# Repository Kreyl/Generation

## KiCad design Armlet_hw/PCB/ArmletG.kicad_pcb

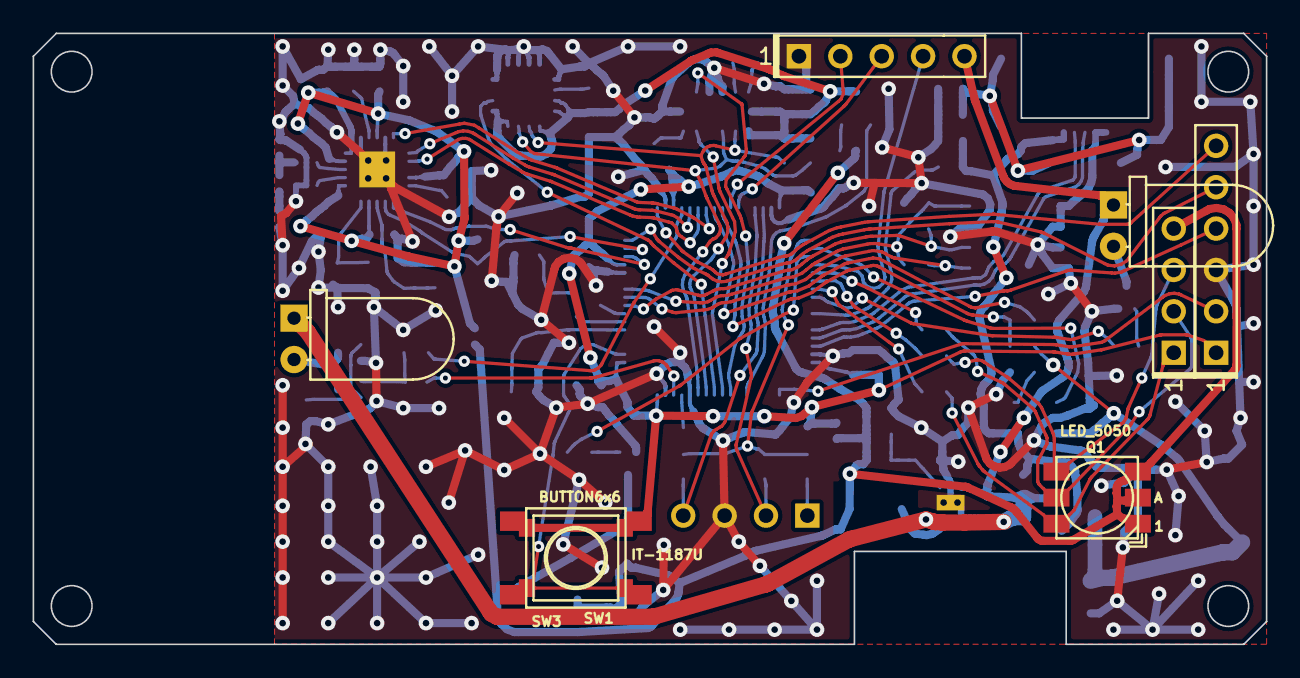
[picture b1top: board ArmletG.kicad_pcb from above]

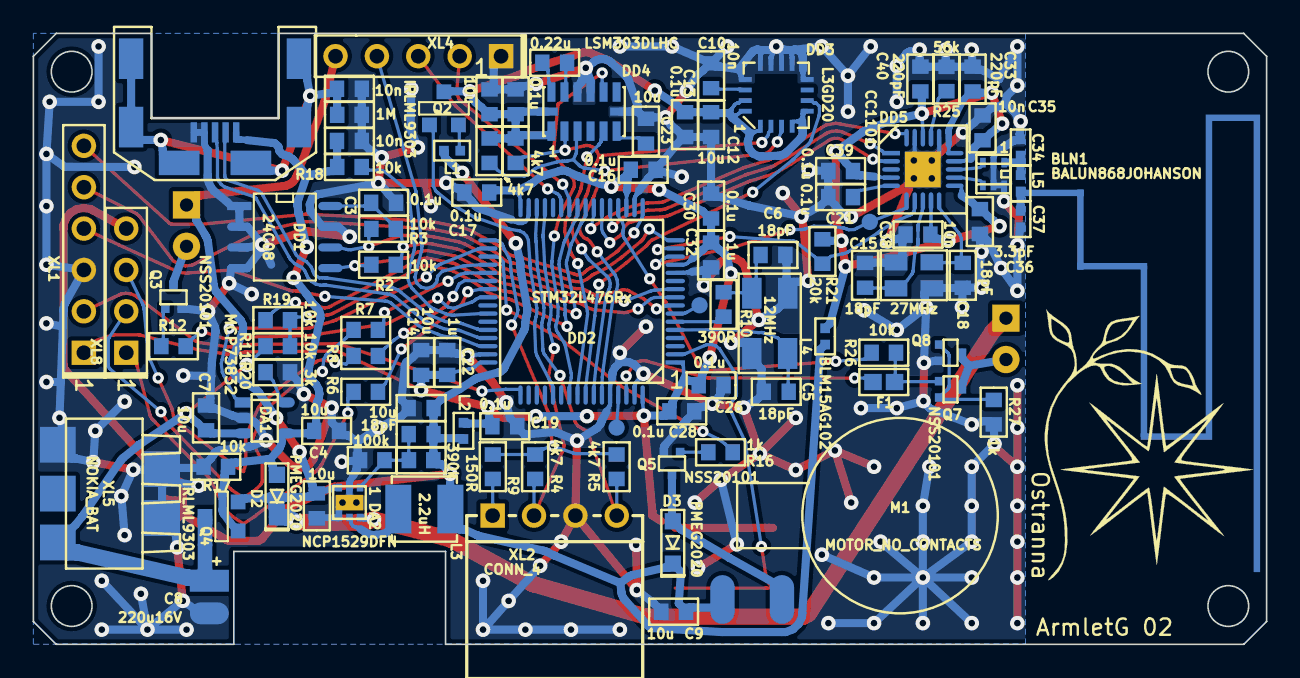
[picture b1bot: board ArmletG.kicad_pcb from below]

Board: 2 copper layers, 75.7 x 37.5 mm, 107 parts (102 on the bottom side), 79 nets.

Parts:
ANT1: ANT_PCB_MONO; ANT_868_ARMLETG
BLN1: BALUN868JOHANSON; BALUN_JOHANSON868
C1, C2, C10, C35, C38: 10n; CAP_0603
C3, C13, C16, C17, C19, C21, C26, C28, C30, C31, C39: 0.1u; CAP_0603
C4, C7, C9, C11, C12, C14, C23, C24, C29: 10u; CAP_0603
C5, C6, C15, C18, C20: 18pF; CAP_0603
C8: 220u16V; CAP_05xxR_horiz_HOLE
C22, C32: 1u; CAP_0603
C25: 0.22u; CAP_0603
C33, C40: 220pF; CAP_0603
C34, C37: *; CAP_0402
C36: 3.3pF; CAP_0603
D1: WhiteLED; LED_Through-Hole-5mm-HOR
D2, D3: PMEG2020; SOD323
D4: LED; LED_Through-Hole-5mm-HOR
DA1: MCP73832; SOT23-5
DA2: NCP1529DFN; DFN6
DD1: 24C08; SO8_150MIL
DD2: STM32L476Rx; LQFP64
DD3: L3GD20; 16_4X4_P065
DD4: LSM303DLHC; 14_5X3_P08
DD5: CC1101; QFN20
F1: Fuse0R; RES_0603_FUSE
L1, L2, L4: BLM15AG102; IND_0402
L3: 2.2uH; IND_1515
L5: *; IND_0402
Logo1: Logo; Ostranna_16d9_13d5
M1: MOTOR_NO_CONTACTS; Motor_no_Contacts
Q1: LED_5050
Q2, Q4: IRLML9303; SOT23-3
Q3, Q5, Q7, Q8: NSS20101; SC89-3
R1: 1M; RES_0603
R2, R3, R17, R18, R19, R20, R26: 10k; RES_0603
R4, R5, R13, R14: 4k7; RES_0603
R6, R7, R8, R12: *; RES_0603
R9: 150R; RES_0603
R10: 390R; RES_0603
R11: 3k; RES_0603
R16, R27: 1k; RES_0603
R21: 20k; RES_0603
R22: 390k; RES_0603
R23: 100k; RES_0603
R25: 56k; RES_0603
SW1: IT-1187U; BTN_4x4_SMD
SW3: BUTTON6x6; BTN_6x6
TP1, TP2, TP3: TESTPOINT; TESTPOINT_1MM
XL1: CONN_6; PLS-6
XL2: CONN_4; PBS-4R
XL3: USB_Micro_B; USBmicro_MOLEX_WM17142
XL4: CONN_5; PLS-5
XL5: NOKIA_BAT; CONN_NOKIA_ACC
XL6, XL7: CONN_1; Oval3x1.5
XL8: CONN_4; PLS-4
XTAL1: 12MHz; 0503x4-4
XTAL2: 27MHz; 03225C4

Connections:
+3.3V: C9.2, C20.2, C24.2, D3.C, L1.2, L2.2, L3.1, L4.2, Q1.1, Q1.2, Q1.3, R22.1, XL6.1, XL8.4
+5V: C2.2, C4.2, D2.A, DA1.4, Q4.1, R17.1, R18.2, XL3.1
+BATT: C7.2, C8.1, DA1.3, Q4.3, R20.2, XL5.1
/ACC_DRDY: DD2.55, DD4.9
/ACC_INT1: DD2.56, DD4.5
/ANT1: BLN1.1, C34.1, L5.2
/ANT2: ANT1.1, C37.1, L5.1
/BLUE_LED: DD2.39, R6.2
/CC_CS: DD2.15, DD5.7, R21.1
/CC_GDO0: DD2.14, DD5.6, TP3.1
/CC_MISO: DD2.22, DD5.2
/CC_MOSI: DD2.23, DD5.20
/CC_SCK: DD2.21, DD5.1
/Charge: DA1.1, DD2.34
/D+: DD2.45, XL3.3
/D-: DD2.44, XL3.2
/GREEN_LED: DD2.38, R8.2
/GYRO_DRDY: DD2.57, DD3.6
/IR_OUT_DAC: DD2.20, R26.2
/IR_OUT_TIM: DD2.62, F1.2
/IR_TX_OUT: D4.C, Q7.3, Q8.3
/LEDW_CTRL: DD2.40, R12.2
/LEDW_OUT: D1.C, Q3.3
/Lout3V3: DA2.5, L3.2
/PWR_ACC: C12.2, C13.2, C29.2, C31.2, DD3.1, DD3.4, DD3.5, DD3.15, DD3.16, DD4.1, DD4.14, Q2.3, R13.1, R14.1
/PWR_ACC_CTRL: DD2.53, Q2.1
/PWR_EE: C3.2, DD1.8, DD2.10, R2.1, R3.2
/PWR_PILL: DD2.33, R4.1, R5.1, R9.1
/PWR_PILL_PROT: R9.2, XL2.1
/RED_LED: DD2.37, R7.2
/RF1: BLN1.4, DD5.12
/RF2: BLN1.3, DD5.13
/SCL_ACC: DD2.58, DD3.2, DD4.2, R13.2
/SCL_EE: DD1.6, DD2.8, R3.1
/SCL_PILL: DD2.29, R4.2, XL2.2
/SDA_ACC: DD2.59, DD3.3, DD4.3, R14.2
/SDA_EE: DD1.5, DD2.9, R2.2
/SDA_PILL: DD2.30, R5.2, XL2.4
/SHLD: C1.2, R1.1, XL3.SHLD
/SWCLK: DD2.49, XL1.2
/SWDIO: DD2.46, XL1.4
/UART_RX: DD2.17, XL1.6
/UART_TX: DD2.16, XL1.5
/VIBRO_OUT: D3.A, Q5.3, XL7.1
/Vibro_CTRL: DD2.35, R16.1
GND: BLN1.2, BLN1.5, BLN1.6, C1.1, C2.1, C3.1, C4.1, C5.2, C6.2, C7.1, C8.2, C9.1, C10.1, C11.1, C12.1, C13.1, C14.1, C15.2, C16.1, C17.1, C18.2, C19.1, C21.1, C22.1, C23.1, C24.1, C26.1, C28.1, C29.1, C30.1, C31.1, C32.1, C33.1, C34.2, C35.1, C36.1, C37.2, C38.1, C39.1, C40.1, DA1.2, DA2.2, DA2.4, DA2.PAD, DD1.1, DD1.2, DD1.3, DD1.4, DD1.7, DD2.12, DD2.18, DD2.31, DD2.47, DD2.60, DD2.63, DD3.8, DD3.9, DD3.10, DD3.11, DD3.12, DD3.13, DD4.7, DD4.10, DD4.11, DD5.16, DD5.19, DD5.PAD, Q3.2, Q5.2, Q8.2, R1.2, R11.2, R17.2, R23.2, R25.2, R27.2, XL1.3, XL2.3, XL3.4, XL3.5, XL4.1, XL5.3, XL5.H, XTAL1.H, XTAL2.H
unnamed: C5.1, DD2.5, XTAL1.1
unnamed: C6.1, R10.1, XTAL1.2
unnamed: C10.2, DD3.14
unnamed: C15.1, DD5.8, XTAL2.1
unnamed: C18.1, DD5.10, XTAL2.2
unnamed: C20.1, DA2.1, R22.2, R23.1
unnamed: C21.2, DD5.5
unnamed: C23.2, DD4.6
unnamed: C25.1, DD4.13
unnamed: C25.2, DD4.12
unnamed: DA1.5, R11.1
unnamed: DD2.2, SW1.2, SW3.1
unnamed: DD2.6, R10.2
unnamed: DD2.7, TP2.1
unnamed: DD2.24, R19.1
unnamed: DD2.25, R19.2, R20.1
unnamed: DD2.26, XL4.2
unnamed: DD2.27, XL4.3
unnamed: DD2.36, XL4.4
unnamed: DD2.42, R18.1
unnamed: DD2.61, TP1.1
unnamed: DD5.17, R25.1
unnamed: F1.1, Q7.1, R26.1
unnamed: L1.1, Q2.2
unnamed: Q1.4, R8.1, XL8.3
unnamed: Q1.5, R7.1, XL8.2
unnamed: Q1.6, R6.1, XL8.1
unnamed: Q3.1, R12.1
unnamed: Q5.1, R16.2
unnamed: Q7.2, Q8.1, R27.1
PwrMCU: C14.2, C16.2, C17.2, C19.2, C22.2, C26.2, C28.2, C30.2, C32.2, DD2.1, DD2.13, DD2.19, DD2.32, DD2.48, DD2.64, L2.1, SW1.1, SW3.2, XL1.1
PwrUnst: C11.2, D1.A, D2.C, D4.A, DA2.3, DA2.6, Q4.2, XL4.5
VCC: C33.2, C35.2, C36.2, C38.2, C39.2, C40.2, DD5.4, DD5.9, DD5.11, DD5.14, DD5.15, DD5.18, L4.1, R21.2

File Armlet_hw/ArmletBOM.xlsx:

Reference | Value | Footprint | Quantity | URL | Price | SolderPoints | PN | SolderPointsDIP | Info | Icc | Sum
ANT1 | ANT_PCB_MONO | Radio:ANT_868_ARMLETG | 1 |  | 0 | 0
BLN1 | BALUN868JOHANSON | Radio:BALUN_JOHANSON868 | 1 | http://onelec.ru/products/0896bm15a0001e-52ab3408-7c12-4b8c-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 | 0 | 6 | 0896BM15A0001E |  |  |  |  | Not needed
C15 C18 C20 C5 C6 | 18pF | Capacitors:CAP_0603 | 5 |  | 0.5 | 2 |  |  |  |  |  | Заказано в AUDS
C1 C10 C2 C35 C38 | 10n | Capacitors:CAP_0603 | 5 |  | 0.5 | 2 |  |  |  |  |  | Есть катушка
C25 | 0.22u | Capacitors:CAP_0603 | 1 |  | 0.5 | 2 |  |  |  |  |  | Заказано в AUDS
C13 C16 C17 C19 C21 C26 C28 C3 C30 C31 C39 | 0.1u | Capacitors:CAP_0603 | 11 |  | 0.5 | 2
C22 C32 | 1u | Capacitors:CAP_0603 | 2 |  | 0.5 | 2 |  |  |  |  |  | Есть катушка
C33 C40 | 220pF | Capacitors:CAP_0603 | 2 |  | 0.5 | 2 |  |  |  |  |  | Not needed
C34 C37 | * | Capacitors:CAP_0402 | 2 |  | 0.5 | 2 |  |  |  |  |  | Not needed
C36 | 3.3pF | Capacitors:CAP_0603 | 1 |  | 0.5 | 2 |  |  |  |  |  | Not needed
C8 | 220u16V | Capacitors:CAP_05xxR_horiz_HOLE | 1 | https://www.terraelectronica.ru/catalog_info.php?CODE=152975 | 7 |  | ECAP 1000/6.3V 0811 105C RD | 2
C11 C12 C14 C23 C24 C29 C4 C7 C9 | 10u | Capacitors:CAP_0603 | 9 | https://www.terraelectronica.ru/catalog.php?ID=1155&search=c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 | 2.5 | 2 | CL10A106MQ8NNNC |  |  |  |  | Заказано в AUDS
D1 | WhiteLED | LEDs:LED_Through-Hole-5mm-HOR | 1 |  | 4 | 2
D2 D3 | PMEG2020 | Diodes:SOD323 | 2 | https://www.terraelectronica.ru/catalog.php?ID=1487&search=p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 | 6.5 | 2 | PMEG2020EJ.115 |  | 2A 20V Vf=525mV
D4 | LED | LEDs:LED_Through-Hole-5mm-HOR | 1 | https://www.terraelectronica.ru/catalog_info.php?CODE=31376 | 4 |  | TSAL6200 | 2 |  |  |  | Not needed
DA1 | MCP73832 | SOT:SOT23-5 | 1 |  | 50 | 5 | MCP73832T-2ACI/OT |  |  |  |  |  | Есть 79, 20 будут через 2 недели
DA2 | NCP1529DFN | QFN_DFN:DFN6 | 1 | https://www.terraelectronica.ru/catalog_info.php?CODE=287423 | 28.9 | 7 | NCP1529MUTBG
DD1 | 24C08 | SO_DIL_TSSOP:SO8_150MIL | 1 | https://www.terraelectronica.ru/catalog_info.php?CODE=328439 | 8.5 | 8 | M24C08-WMN6P |  |  | 1
DD2 | STM32L476Rx | LQFP_TQFP:LQFP64 | 1 |  | 290 | 64 | STM32L476RCT6
DD3 | L3GD20 | LGA:16_4X4_P065 | 1 | https://www.terraelectronica.ru/catalog_info.php?CODE=878736 | 178 | 16 | L3GD20 |  |  | 6.2
DD4 | LSM303DLHC | LGA:14_5X3_P08 | 1 | https://www.terraelectronica.ru/catalog_info.php?CODE=685189 | 278 | 14 | LSM303DLHC |  |  | 0.12
DD5 | CC1101 | QFN_DFN:QFN20 | 1 | http:// | 140 | 21 |  |  |  |  |  | Not needed
F1 | Fuse0R | Resistors:RES_0603_FUSE | 1 |  | 0 | 1
L3 | 2.2uH | Inductors:IND_1515 | 1 | https://www.terraelectronica.ru/catalog.php?ID=422&search=lq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 | 18.5 | 2 | LQH44PN2R2 |  | 1.8A 0.05R 70MHz
L1 L2 L4 | BLM15AG102 | Inductors:IND_0402 | 3 |  | 1 | 2 | BLM15AG102SN1
L5 | * | Inductors:IND_0402 | 1 |  | 4 | 2 |  |  |  |  |  | Not needed
M1 | MOTOR_NO_CONTACTS | Installation:Motor_no_Contacts | 1 | http://www.aliexpress.com/item/100pcs-lot-Model-1227-Voltage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 | 28 | 0 |  |  |  |  |  | Есть 74, остальные возьмём в медальонах
Q1 | LED_5050 | LEDs:LED_5050 | 1 |  | 7 | 6
Q2 Q4 | IRLML9303 | SOT:SOT23-3 | 2 | https://www.terraelectronica.ru/catalog.php?ID=349&search=irlml9303 | 7 | 3 | IRLML9303TRPBF
Q3 Q5 Q7 Q8 | NSS20101 | SOT:SC89-3 | 4 | https://www.terraelectronica.ru/catalog.php?ID=356&search=nss20101 | 5 | 3 | NSS20101JT1G
R1 | 1M | Resistors:RES_0603 | 1 |  | 0.5 | 2 |  |  |  |  |  | Есть катушка
R10 | 390R | Resistors:RES_0603 | 1 |  | 0.5 | 2 |  |  |  |  |  | Not needed
R11 | 3k | Resistors:RES_0603 | 1 |  | 0.5 | 2 |  |  |  |  |  | Заказано в AUDS
R16 R27 | 1k | Resistors:RES_0603 | 2 |  | 0.5 | 2 |  |  |  |  |  | Есть катушка
R21 | 20k | Resistors:RES_0603 | 1 |  | 0.5 | 2
R22 | 390k | Resistors:RES_0603 | 1 |  | 0.5 | 2 |  |  |  |  |  | Заказано в AUDS
R23 | 100k | Resistors:RES_0603 | 1 |  | 0.5 | 2 |  |  |  |  |  | Есть катушка
R25 | 56k | Resistors:RES_0603 | 1 |  | 0.5 | 2 |  |  |  |  |  | Not needed
R17 R18 R19 R2 R20 R26 R3 | 10k | Resistors:RES_0603 | 7 |  | 0.5 | 2 |  |  |  |  |  | Есть катушка
R13 R14 R4 R5 | 4k7 | Resistors:RES_0603 | 4 |  | 0.5 | 2 |  |  |  |  |  | Заказано в AUDS
R12 R6 R7 R8 | * | Resistors:RES_0603 | 4 |  | 0.5 | 2
R9 | 150R | Resistors:RES_0603 | 1 |  | 0.5 | 2
SW1 | IT-1187U | BtnsSwitches:BTN_4x4_SMD | 1 | http://www.zip-2002.ru/kommutatsiya/taktovye_knopki/83334/it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 | 4.5 | 4 |  |  |  |  |  | Not needed
SW3 | BUTTON6x6 | BtnsSwitches:BTN_6x6 | 1 |  | 1 | 4 |  |  |  |  |  | Not needed
TP1 TP2 TP3 | TESTPOINT | PCB:TESTPOINT_1MM | 3 |  | 0 | 0
XL1 | CONN_6 | Connectors:PLS-6 | 1 |  |  |  |  | 6
XL2 | CONN_4 | Connectors:PBS-4R | 1 | http://www.berelcom.ru/shop/show_good.php?idtov=1200014096&grid= | 4 | 0 | PBS-4R | 4
XL3 | USB_Micro_B | Connectors:USBmicro_MOLEX_WM17142 | 1 | https://www.terraelectronica.ru/catalog_info.php?CODE=281706 | 53.5 | 11 | 47491-0001 MOLEX
XL4 | CONN_5 | Connectors:PLS-5 | 1
XL5 | NOKIA_BAT | Connectors:CONN_NOKIA_ACC | 1 |  | 25 | 5 |  |  | For BL-5C
XL6 XL7 | CONN_1 | PCB:Oval3x1.5 | 2 |  | 0 | 1
XL8 | CONN_4 | Connectors:PLS-4 | 1 |  |  | 0 |  | 4
XTAL1 | 12MHz | Quartz:0503x4-4 | 1 |  | 15 | 4 |  |  |  |  |  | Not needed
XTAL2 | 27MHz | Quartz:03225C4 | 1 |  | 15 | 4 |  |  |  |  |  | Not needed

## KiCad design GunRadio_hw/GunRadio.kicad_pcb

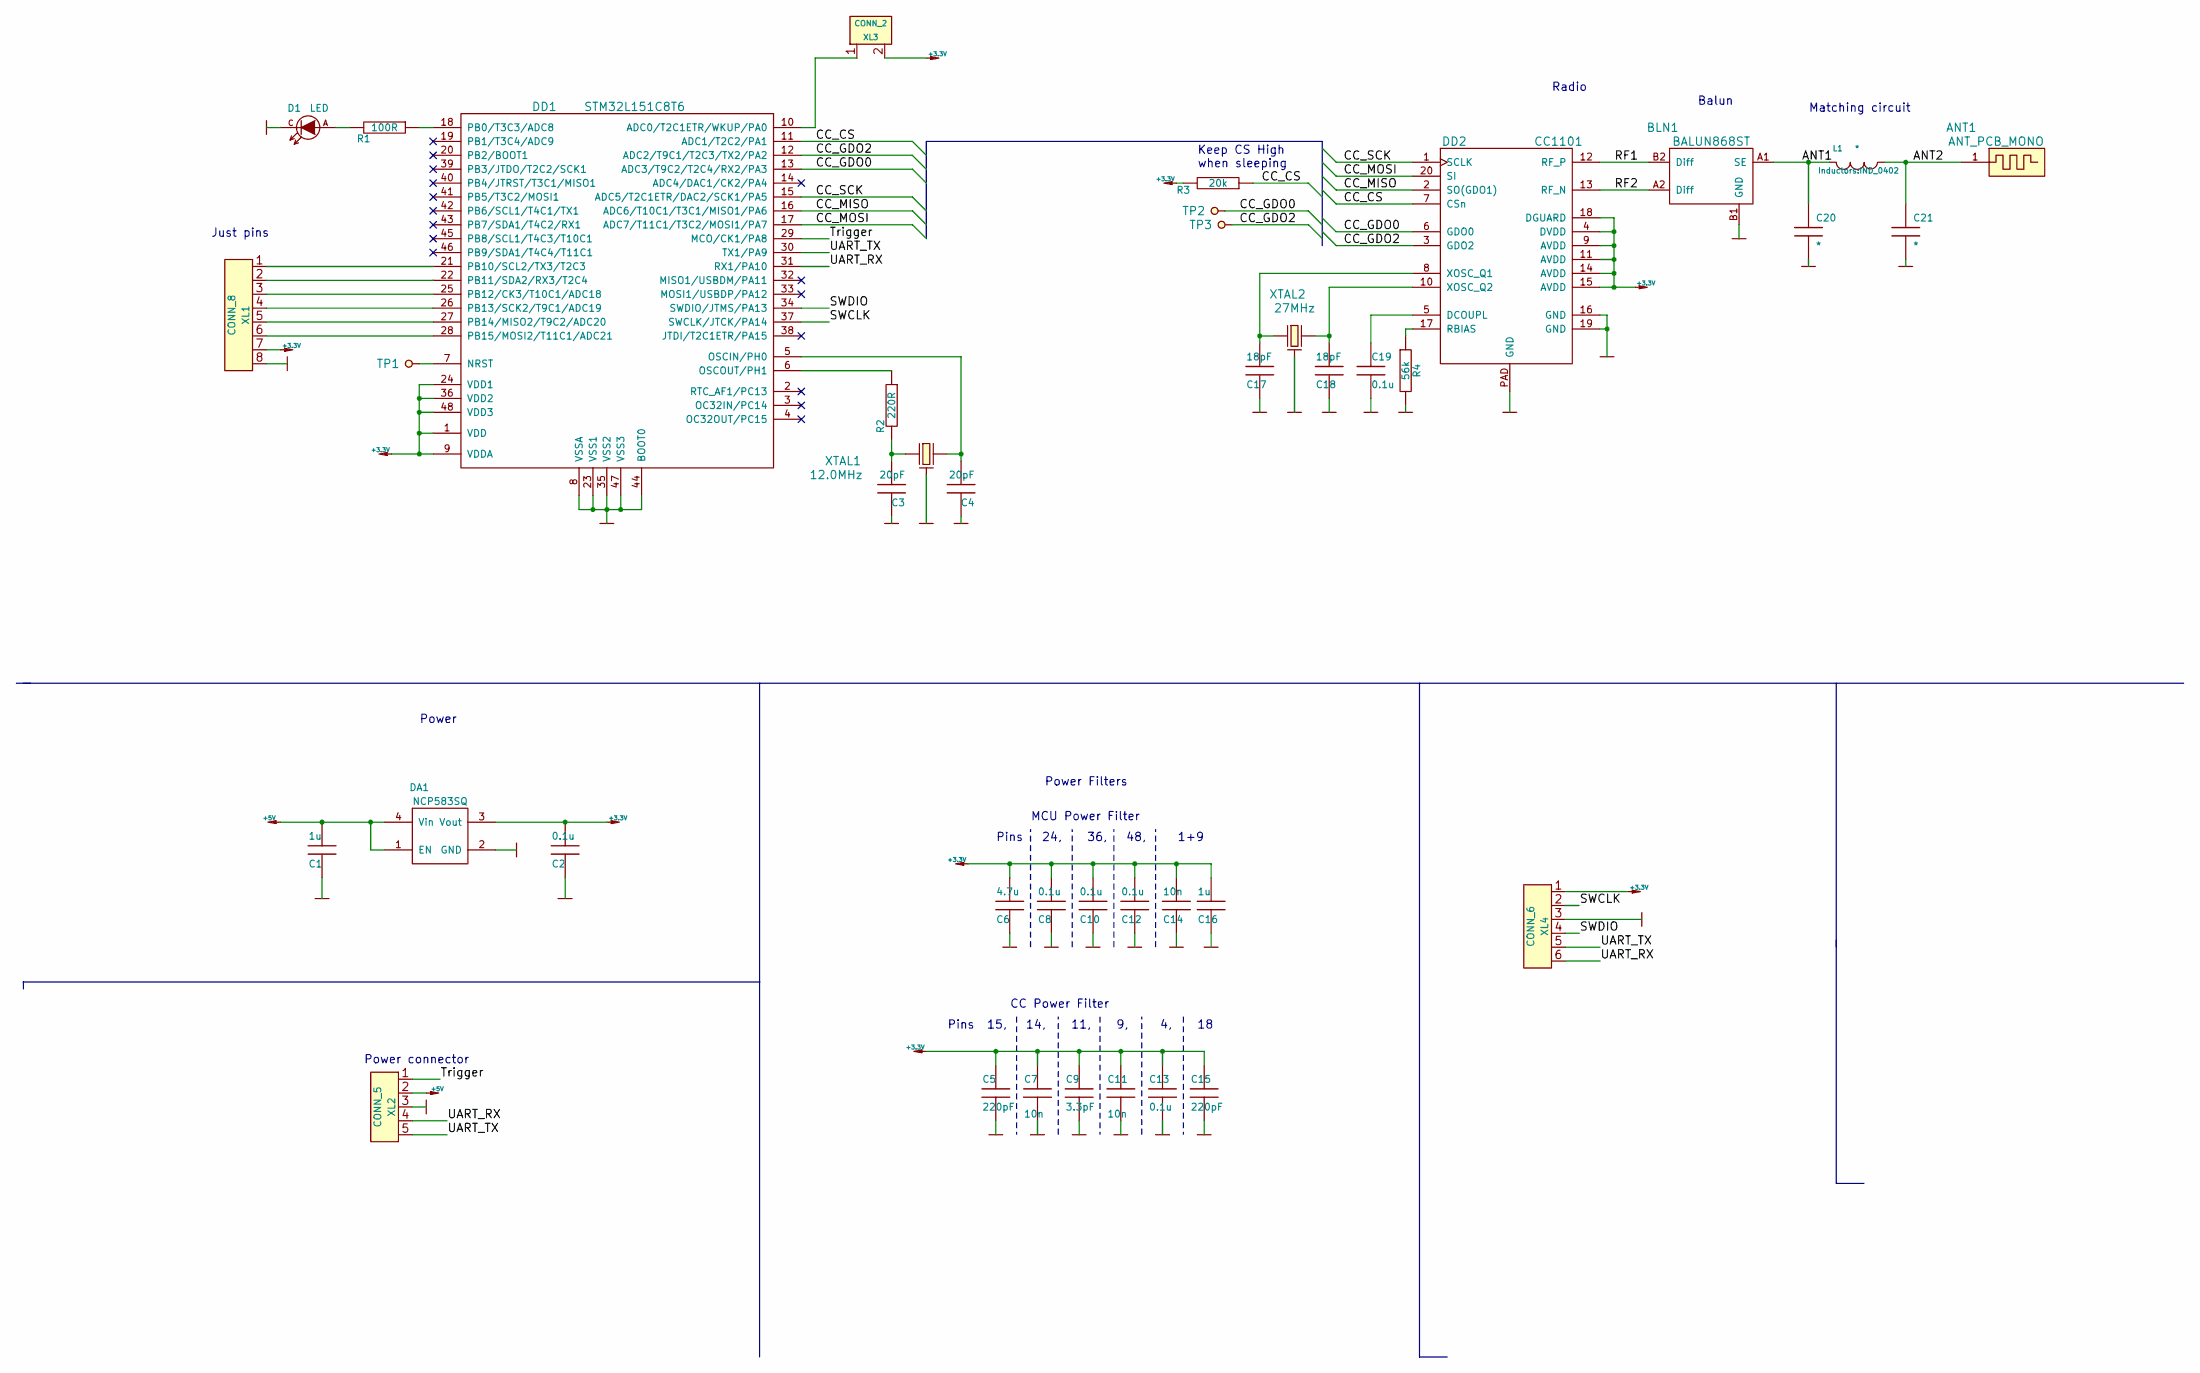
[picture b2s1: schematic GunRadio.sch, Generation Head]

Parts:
ANT1: ANT_PCB_MONO; ANT_868_GunRADIO
BLN1: BALUN868ST; BALUN868_ST
C1, C16: 1u; CAP_0603
C2, C8, C10, C12, C13, C19: 0.1u; CAP_0603
C3, C4: 20pF; CAP_0603
C5, C15: 220pF; CAP_0603
C6: 4.7u; CAP_0603
C7, C11, C14: 10n; CAP_0603
C9: 3.3pF; CAP_0603
C17, C18: 18pF; CAP_0603
C20, C21: *; CAP_0402
D1: LED; LED_0603
DA1: NCP583SQ; SC82AB
DD1: STM32L151C8T6; LQFP48
DD2: CC1101; QFN20
L1: *; IND_0402
R1: 100R; RES_0603
R2: 220R; RES_0603
R3: 20k; RES_0603
R4: 56k; RES_0603
TP1, TP2, TP3: TESTPOINT; TESTPOINT_1MM
XL1: CONN_8; PLS-8
XL2: CONN_5; PLS-5
XL3: CONN_2; PLS-2
XL4: CONN_6; PLS-6
XTAL1: 12.0MHz; 0503x4-4
XTAL2: 27MHz; 03225C4

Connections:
+3.3V: C2.1, C5.1, C6.1, C7.1, C8.1, C9.1, C10.1, C11.1, C12.1, C13.1, C14.1, C15.1, C16.1, DA1.3 (Vout), DD1.1 (VDD), DD1.9 (VDDA), DD1.24 (VDD1), DD1.36 (VDD2), DD1.48 (VDD3), DD2.4 (DVDD), DD2.9 (AVDD), DD2.11 (AVDD), DD2.14 (AVDD), DD2.15 (AVDD), DD2.18 (DGUARD), R3.2, XL1.7, XL3.2 (PM), XL4.1
+5V: C1.1, DA1.1 (EN), DA1.4 (Vin), XL2.2
/ANT1: BLN1.A1 (SE), C20.1, L1.2
/ANT2: ANT1.1, C21.1, L1.1
/CC_CS: DD1.11 (ADC1/T2C2/PA1), DD2.7 (CSn), R3.1
/CC_GDO0: DD1.13 (ADC3/T9C2/T2C4/RX2/PA3), DD2.6 (GDO0), TP2.1
/CC_GDO2: DD1.12 (ADC2/T9C1/T2C3/TX2/PA2), DD2.3 (GDO2), TP3.1
/CC_MISO: DD1.16 (ADC6/T10C1/T3C1/MISO1/PA6), DD2.2 (SO(GDO1))
/CC_MOSI: DD1.17 (ADC7/T11C1/T3C2/MOSI1/PA7), DD2.20 (SI)
/CC_SCK: DD1.15 (ADC5/T2C1ETR/DAC2/SCK1/PA5), DD2.1 (SCLK)
/RF1: BLN1.B2 (Diff), DD2.12 (RF_P)
/RF2: BLN1.A2 (Diff), DD2.13 (RF_N)
/SWCLK: DD1.37 (SWCLK/JTCK/PA14), XL4.2
/SWDIO: DD1.34 (SWDIO/JTMS/PA13), XL4.4
/Trigger: DD1.29 (MCO/CK1/PA8), XL2.1
/UART_RX: DD1.31 (RX1/PA10), XL2.4, XL4.6
/UART_TX: DD1.30 (TX1/PA9), XL2.5, XL4.5
GND: BLN1.B1 (GND), C1.2, C2.2, C3.2, C4.2, C5.2, C6.2, C7.2, C8.2, C9.2, C10.2, C11.2, C12.2, C13.2, C14.2, C15.2, C16.2, C17.2, C18.2, C19.2, C20.2, C21.2, D1.C, DA1.2 (GND), DD1.8 (VSSA), DD1.23 (VSS1), DD1.35 (VSS2), DD1.44 (BOOT0), DD1.47 (VSS3), DD2.16 (GND), DD2.19 (GND), DD2.PAD (GND), R4.2, XL1.8, XL2.3, XL4.3, XTAL1.H, XTAL2.H
unnamed: C3.1, R2.2, XTAL1.1
unnamed: C4.1, DD1.5 (OSCIN/PH0), XTAL1.2
unnamed: C17.1, DD2.8 (XOSC_Q1), XTAL2.1
unnamed: C18.1, DD2.10 (XOSC_Q2), XTAL2.2
unnamed: C19.1, DD2.5 (DCOUPL)
unnamed: D1.A, R1.2
unnamed: DD1.6 (OSCOUT/PH1), R2.1
unnamed: DD1.7 (NRST), TP1.1
unnamed: DD1.10 (ADC0/T2C1ETR/WKUP/PA0), XL3.1
unnamed: DD1.18 (PB0/T3C3/ADC8), R1.1
unnamed: DD1.21 (PB10/SCL2/TX3/T2C3), XL1.1
unnamed: DD1.22 (PB11/SDA2/RX3/T2C4), XL1.2
unnamed: DD1.25 (PB12/CK3/T10C1/ADC18), XL1.3
unnamed: DD1.26 (PB13/SCK2/T9C1/ADC19), XL1.4
unnamed: DD1.27 (PB14/MISO2/T9C2/ADC20), XL1.5
unnamed: DD1.28 (PB15/MOSI2/T11C1/ADC21), XL1.6
unnamed: DD2.17 (RBIAS), R4.1

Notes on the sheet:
Radio
Matching circuit
Balun
MCU Power Filter
Pins 24, 36, 48, 1+9
CC Power Filter
Pins 15, 14, 11, 9, 4, 18
Keep CS High when sleeping
Power
Power Filters
Just pins
Power connector

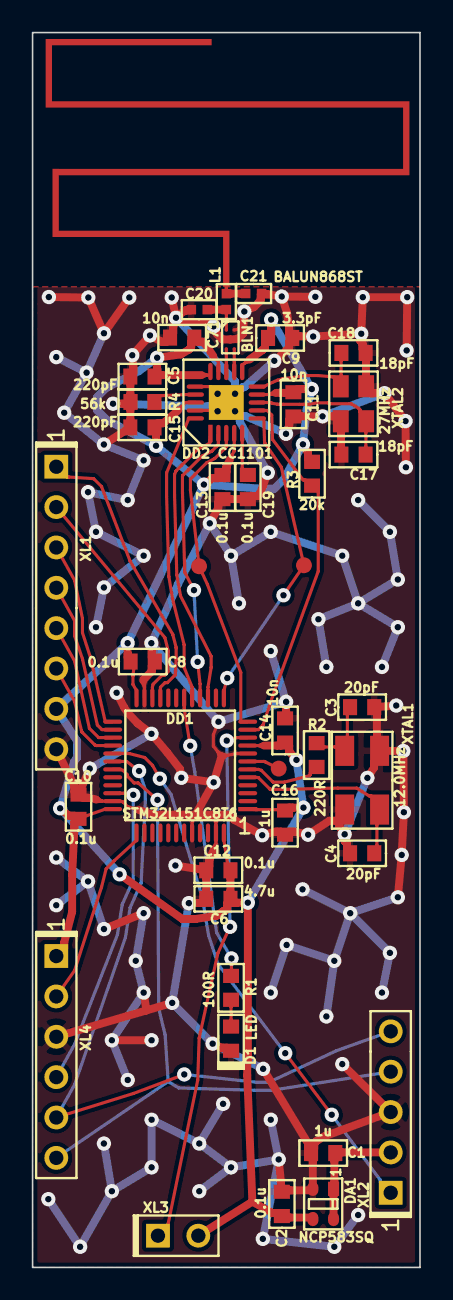
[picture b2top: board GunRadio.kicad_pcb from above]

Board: 2 copper layers, 24.4 x 77.7 mm, 41 parts (0 on the bottom side), 35 nets.

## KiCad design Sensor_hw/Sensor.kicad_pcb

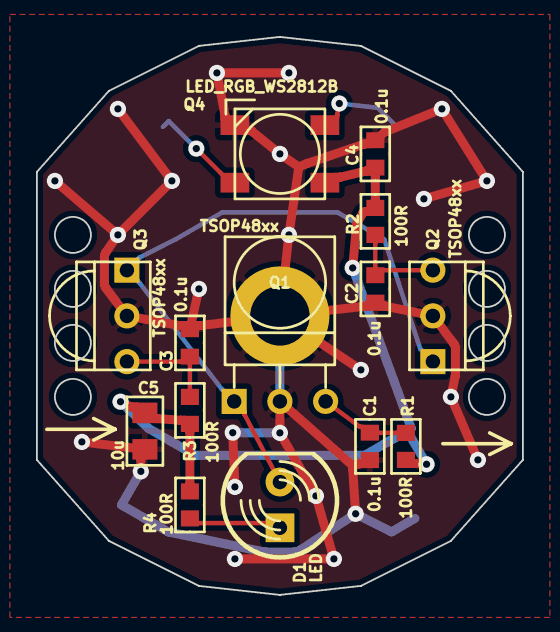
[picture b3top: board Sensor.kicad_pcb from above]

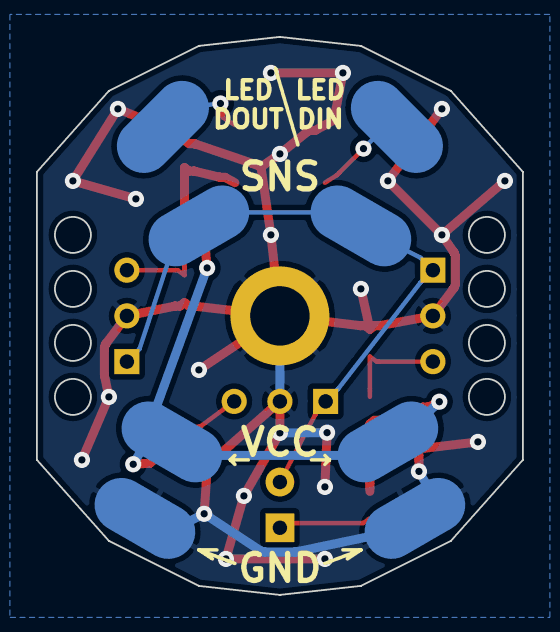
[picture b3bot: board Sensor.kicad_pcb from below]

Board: 2 copper layers, 27.0 x 31.0 mm, 23 parts (8 on the bottom side), 9 nets.

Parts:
C1, C2, C3, C4: 0.1u; CAP_0603
C5: 10u; CAP_0805
D1: LED; LED_Through-Hole-5mm
HOLE1: HOLE_METALLED; Hole3d3_out5d5mm
Q1: TSOP48xx; TSOP48xx_Horiz
Q2, Q3: TSOP48xx
Q4: LED_RGB_WS2812B; LED_WS2812B
R1, R2, R3, R4: 100R; RES_0603
XL1, XL2, XL3, XL4, XL5, XL6, XL7, XL8: CONN_1; Oval6x3

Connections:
/LED_DIN: Q4.4, XL4.1
/LED_DOUT: Q4.2, XL8.1
/SNS: D1.C, Q1.1, Q2.1, Q3.1, XL3.1, XL7.1
GND: C1.2, C2.2, C3.2, C4.2, C5.2, HOLE1.H, Q1.2, Q2.2, Q3.2, Q4.3, XL1.1, XL5.1
unnamed: C1.1, Q1.3, R1.2
unnamed: C2.1, Q2.3, R2.2
unnamed: C3.1, Q3.3, R3.2
unnamed: D1.A, R4.1
VCC: C4.1, C5.1, Q4.1, R1.1, R2.1, R3.1, R4.2, XL2.1, XL6.1

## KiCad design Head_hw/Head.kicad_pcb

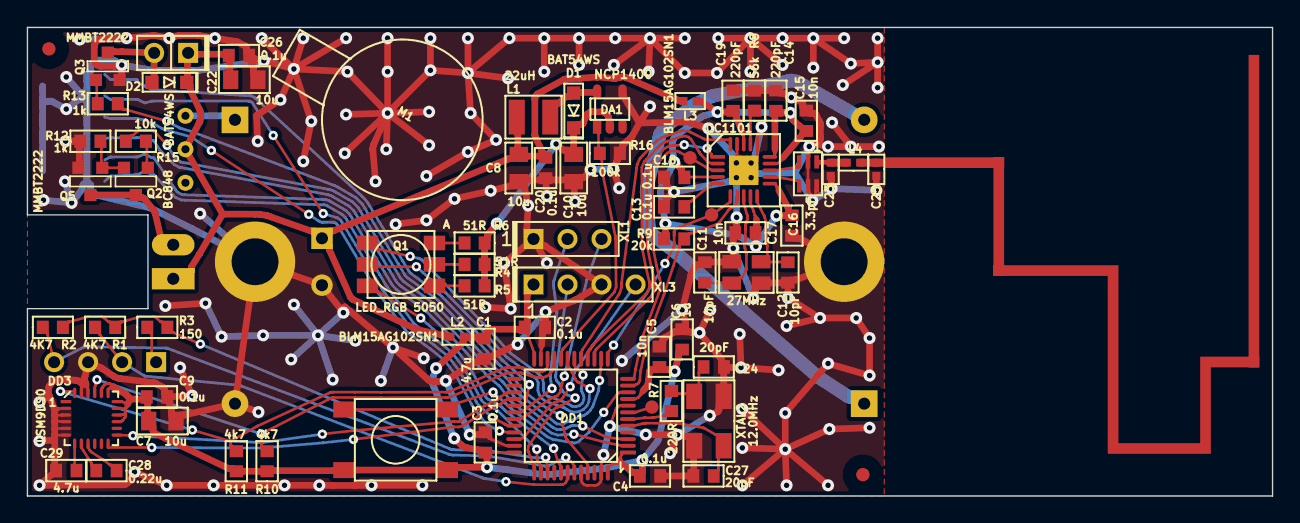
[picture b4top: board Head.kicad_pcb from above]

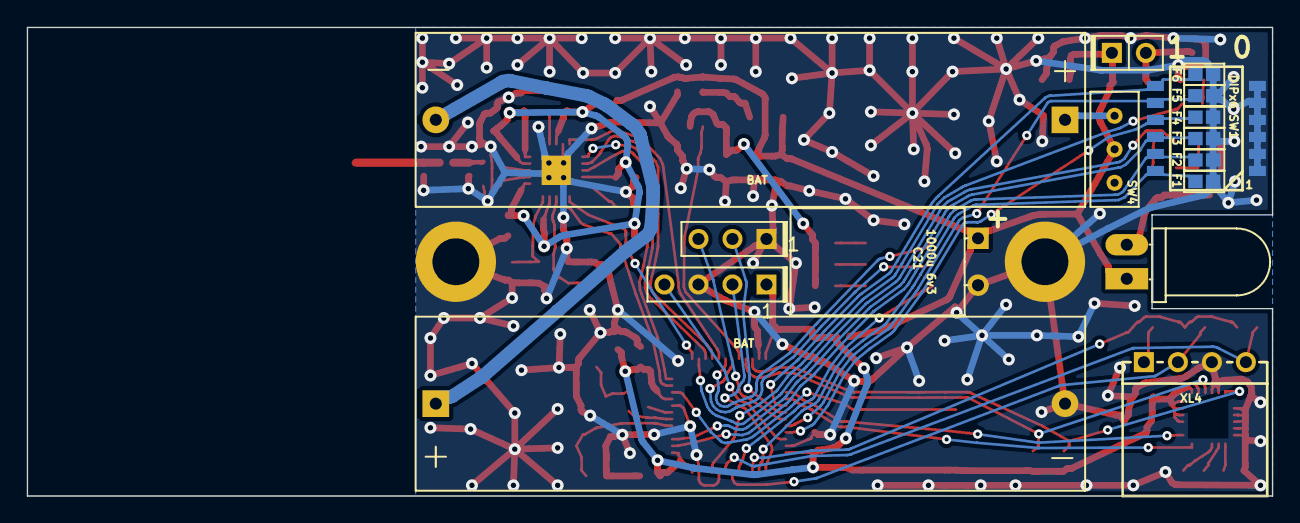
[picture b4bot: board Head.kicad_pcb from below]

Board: 2 copper layers, 93.0 x 35.0 mm, 86 parts (13 on the bottom side), 62 nets.

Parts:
ANT1: ANT_PCB_MONO; ANT_868_MEANDER_4HOR_35mm
B1, B2: BAT; BATTERY_AAA_X1
BLN1: 0896BM15A0001; BALUN_JOHANSON868
C1, C29: 4.7u; CAP_0603
C2, C3, C4, C9, C13, C18, C20, C26: 0.1u; CAP_0603
C5, C15, C17: 10n; CAP_0603
C6: 1u; CAP_0603
C7, C8, C10, C22: 10u; CAP_0805
C11, C12: 10pF; CAP_0603
C14, C19: 220pF; CAP_0603
C16: 3.3pF; CAP_0603
C21: 1000u 6v3; CAP_08xxR_HOR
C23: 1.5pF; CAP_0402
C24, C27: 20pF; CAP_0603
C25: DoNotMount; CAP_0402
C28: 0.22u; CAP_0603
D1, D2: BAT54WS; SOD323
D3: LED; LED_SMD-5mm-HOR_mirr
DA1: NCP1400; SOT23-5
DD1: STM32L151CxTx; LQFP48
DD2: CC1101; QFN20
DD3: LSM9DS0; 24_4X4_P05
F1, F2, F3, F4, F5, F6: Fuse0R; RES_0603_FUSE
HOLE1, HOLE2: HOLE_METALLED; Hole3_5_out6mm
L1: 22uH; IND_1210_LQH32C
L2, L3: BLM15AG102SN1; IND_0402
L4: 5.6nH; IND_0402
M1: MOTOR_NO_CONTACTS; Motor_no_Contacts
Q1: LED_RGB 5050; 5050
Q2: BC848; SOT23-3
Q3, Q5: MMBT2222; SOT23-3
R1, R2: 4K7; RES_0603
R3: 150; RES_0603
R4, R5, R6: 51R; RES_0603
R7: 220R; RES_0603
R8: 56k; RES_0603
R9: 20k; RES_0603
R10, R11: 4k7; RES_0603
R12, R13: 1k; RES_0603
R15: 10k; RES_0603
R16: 100k; RES_0603
RP1, RP2: REFPOINT; REF_POINT_1MM
SW1: DIPx6; DIP_SMD_1D27X6
SW2: BUTTON; BTN_6x6
SW4: SWITCH; SW_SS-1P2T
TP1, TP2, TP3: TESTPOINT; TESTPOINT_1MM
XL1: CONN_3; PLS-3
XL3: ST_SWD; PLS-4
XL4: CONN_4; PBS-4R
XL6: CONN_2; PLS-2
XTAL1: 27MHz; 03225C4
XTAL2: 12.0MHz; 0503x4-4

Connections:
+3.3V: C10.1, D1.C, DA1.2, R4.1, R5.1, R6.1
+BATT: C8.1, C20.1, C21.1, C22.1, C26.1, D2.C, D3.A, L1.2, L2.2, L3.2, SW4.2, XL6.1
/ACC_INT1: DD1.27, DD3.13
/ANT1: BLN1.1, C23.1, L4.2
/ANT2: ANT1.1, C25.1, L4.1
/BAT_BTW: B1.C, B2.A
/BAT_IN: B1.A, SW4.1
/BLUE_LED: DD1.18, Q1.BC
/CC_CS: DD1.11, DD2.7, R9.1
/CC_GDO0: DD1.13, DD2.6, TP2.1
/CC_GDO2: DD1.12, DD2.3, TP3.1
/CC_MISO: DD1.16, DD2.2
/CC_MOSI: DD1.17, DD2.20
/CC_SCK: DD1.15, DD2.1
/DS1: DD1.38, F1.1, SW1.12
/DS2: DD1.2, F2.1, SW1.11
/DS3: DD1.3, F3.1, SW1.10
/DS4: DD1.33, F4.1, SW1.9
/DS5: DD1.32, F5.1, SW1.8
/DS6: DD1.29, F6.1, SW1.7
/GREEN_LED: DD1.41, Q1.GC
/GYRO_DRDY: DD1.28, DD3.12
/I2C_SCL: DD1.21, DD3.21, R10.2
/I2C_SDA: DD1.22, DD3.24, R11.1
/IR_LED: DD1.14, R15.1
/IR_LED_OUT: D3.C, Q2.3, Q5.3
/LED_EN: DA1.1, DD1.20, R16.1
/Lout: D1.A, DA1.5, L1.1
/P_SCL: DD1.42, R1.1, XL4.2
/P_SDA: DD1.43, R2.1, XL4.4
/PeriphPwr: DD1.39, R1.2, R2.2, R3.2
/PeriphPwr1: R3.1, XL4.1
/RED_LED: DD1.19, Q1.RC
/RF1: BLN1.4, DD2.12
/RF2: BLN1.3, DD2.13
/SWCLK: DD1.37, XL3.2
/SWDIO: DD1.34, XL3.4
/UART_RX: DD1.31, XL1.3
/UART_TX: DD1.30, XL1.2
/Vibro: DD1.45, R13.1
/VibroOut: D2.A, Q3.3, XL6.2
GND: B2.C, BLN1.2, BLN1.5, BLN1.6, C1.2, C2.2, C3.2, C4.2, C5.2, C6.2, C7.2, C8.2, C9.2, C10.2, C11.2, C12.2, C13.2, C14.2, C15.2, C16.2, C17.2, C18.2, C19.2, C20.2, C21.2, C22.2, C23.2, C24.2, C25.2, C26.2, C27.2, C29.1, DA1.4, DD1.8, DD1.23, DD1.35, DD1.44, DD1.47, DD2.16, DD2.19, DD2.PAD, DD3.2, DD3.3, DD3.4, DD3.5, DD3.6, DD3.22, DD3.23, F1.2, F2.2, F3.2, F4.2, F5.2, F6.2, HOLE1.H, HOLE2.H, Q3.2, Q5.2, R8.2, R12.1, R16.2, SW1.1, SW1.2, SW1.3, SW1.4, SW1.5, SW1.6, XL1.1, XL3.3, XL4.3, XTAL1.H, XTAL2.H
unnamed: C11.1, DD2.8, XTAL1.1
unnamed: C12.1, DD2.10, XTAL1.2
unnamed: C13.1, DD2.5
unnamed: C24.1, R7.2, XTAL2.1
unnamed: C27.1, DD1.5, XTAL2.2
unnamed: C28.1, DD3.9
unnamed: C28.2, DD3.8
unnamed: C29.2, DD3.7
unnamed: DD1.6, R7.1
unnamed: DD1.7, TP1.1
unnamed: DD1.10, SW2.1
unnamed: DD2.17, R8.1
unnamed: Q1.BA, R6.2
unnamed: Q1.GA, R5.2
unnamed: Q1.RA, R4.2
unnamed: Q2.1, R15.2
unnamed: Q2.2, Q5.1, R12.2
unnamed: Q3.1, R13.2
PwrMCU: C1.1, C2.1, C3.1, C4.1, C5.1, C6.1, C7.1, C9.1, DD1.1, DD1.9, DD1.24, DD1.36, DD1.48, DD3.15, DD3.16, DD3.17, DD3.18, DD3.19, DD3.20, L2.1, R10.1, R11.2, SW2.2, XL3.1
VCC: C14.1, C15.1, C16.1, C17.1, C18.1, C19.1, DD2.4, DD2.9, DD2.11, DD2.14, DD2.15, DD2.18, L3.1, R9.2

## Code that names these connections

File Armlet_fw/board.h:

/*
 * board.h
 *
 *  Created on: 12 ñåíò. 2015 ã.
 *      Author: Kreyl
 */

#pragma once

#include <inttypes.h>

// ==== General ====
#define BOARD_NAME          "ArmletG"

#define DEBUG_OTK           0

// MCU type as defined in the ST header.
#define STM32L476xx

// Freq of external crystal if any. Leave it here even if not used.
#define CRYSTAL_FREQ_HZ 12000000

// OS timer settings
#define STM32_ST_IRQ_PRIORITY   2
#define STM32_ST_USE_TIMER      5
#define SYS_TIM_CLK             (Clk.APB1FreqHz)    // Timer 5 is clocked by APB1

//  Periphery
#define I2C1_ENABLED            TRUE
#define I2C2_ENABLED            TRUE
#define I2C3_ENABLED            TRUE

#define ADC_REQUIRED            FALSE
#define STM32_DMA_REQUIRED      TRUE    // Leave this macro name for OS

#if 1 // ========================== GPIO =======================================
// UART
#define UART_GPIO       GPIOA
#define UART_TX_PIN     2
#define UART_RX_PIN     3
#define UART_AF         AF7 // for all USARTs

// RGB LED
#define LED_RED_CH      { GPIOC, 6, TIM3, 1, invInverted, omPushPull, 255 }
#define LED_GREEN_CH    { GPIOC, 7, TIM3, 2, invInverted, omPushPull, 255 }
#define LED_BLUE_CH     { GPIOC, 8, TIM3, 3, invInverted, omPushPull, 255 }
// White LED
#define LED_WHITE       { GPIOC, 9, TIM3, 4 }
// IR LED
//#define LED_IR          { GPIOA, 4 }

// Vibro
#define VIBRO_TOP       100
#define VIBRO_PIN       { GPIOB, 15, TIM15, 2, invNotInverted, omPushPull, VIBRO_TOP }

// Beeper
#define BEEPER_TOP      22
#define BEEPER_PIN      { GPIOB, 9, TIM17, 1, invNotInverted, omPushPull, BEEPER_TOP }

// Mems
#define MEMS_PWR_GPIO   GPIOC
#define MEMS_PWR_PIN    12

// I2C
#define I2C1_GPIO       GPIOB
#define I2C1_SCL        6
#define I2C1_SDA        7
#define I2C2_GPIO       GPIOB
#define I2C2_SCL        10
#define I2C2_SDA        11
#define I2C3_GPIO       GPIOC
#define I2C3_SCL        0
#define I2C3_SDA        1
// I2C Alternate Function
#define I2C_AF          AF4

// Pill power
#define PILL_PWR_PIN    { GPIOB, 12, omPushPull }
// EE power
#define EE_PWR_PIN      { GPIOC, 2, omPushPull }

//  Battery measurement
#define BAT_GND_PIN     GPIOC, 4, omPushPull
#define BAT_INPUT_PIN   GPIOC, 5

// State pins
#define USB_DETECT_PIN  GPIOA, 9
#define CHARGE_PIN      GPIOB, 13

// Radio
#define CC_GPIO         GPIOA
#define CC_GDO2         NC
#define CC_GDO0         0
#define CC_SCK          5
#define CC_MISO         6
#define CC_MOSI         7
#define CC_CS           1
// Input pin
#define CC_GDO0_IRQ     { CC_GPIO, CC_GDO0, pudNone }

#endif // GPIO

#if 1 // ========================= Timer =======================================
//#define TMR_DAC_CHUNK               TIM6
//#define TMR_DAC_SMPL                TIM7
//#define TMR_DAC_CHUNK_IRQ           TIM6_IRQn
//#define TMR_DAC_CHUNK_IRQ_HANDLER   VectorEC
#endif // Timer

#if I2C_REQUIRED // ====================== I2C =================================

#endif

#if 1 // =========================== SPI =======================================
#define CC_SPI          SPI1
#define CC_SPI_AF       AF5
#endif

#if 1 // ========================== USART ======================================
#define PRINTF_FLOAT_EN TRUE
#define UART            USART2
#define UART_TX_REG     UART->TDR
#define UART_RX_REG     UART->RDR
#endif

#if ADC_REQUIRED // ======================= Inner ADC ==========================
// Clock divider: clock is generated from the APB2
#define ADC_CLK_DIVIDER		adcDiv2

// ADC channels
#define ADC_BATTERY_CHNL 	14
// ADC_VREFINT_CHNL
#define ADC_CHANNELS        { ADC_BATTERY_CHNL, ADC_VREFINT_CHNL }
#define ADC_CHANNEL_CNT     2   // Do not use countof(AdcChannels) as preprocessor does not know what is countof => cannot check
#define ADC_SAMPLE_TIME     ast24d5Cycles
#define ADC_OVERSAMPLING_RATIO  64   // 1 (no oversampling), 2, 4, 8, 16, 32, 64, 128, 256
#endif

#if 1 // =========================== DMA =======================================
// ==== Uart ====
// Remap is made automatically if required
#define UART_DMA_TX     STM32_DMA1_STREAM7
#define UART_DMA_RX     STM32_DMA1_STREAM6
#define UART_DMA_CHNL   2

// DAC
//#define DAC_DMA         STM32_DMA1_STREAM2

// ==== I2C ====
#define I2C1_DMA_TX     STM32_DMA2_STREAM7
#define I2C1_DMA_RX     STM32_DMA2_STREAM6
#define I2C1_DMA_CHNL   5
#define I2C2_DMA_TX     STM32_DMA1_STREAM4
#define I2C2_DMA_RX     STM32_DMA1_STREAM5
#define I2C2_DMA_CHNL   3
#define I2C3_DMA_TX     STM32_DMA1_STREAM2
#define I2C3_DMA_RX     STM32_DMA1_STREAM3
#define I2C3_DMA_CHNL   3

//#define STM32_I2C_I2C3_RX_DMA_STREAM   STM32_DMA_STREAM_ID(1, 3)
//#define STM32_I2C_I2C3_TX_DMA_STREAM   STM32_DMA_STREAM_ID(1, 2)


#if ADC_REQUIRED
#define ADC_DMA         STM32_DMA1_STREAM1
#define ADC_DMA_MODE    STM32_DMA_CR_CHSEL(0) |   /* DMA1 Stream1 Channel0 */ \
                        DMA_PRIORITY_LOW | \
                        STM32_DMA_CR_MSIZE_HWORD | \
                        STM32_DMA_CR_PSIZE_HWORD | \
                        STM32_DMA_CR_MINC |       /* Memory pointer increase */ \
                        STM32_DMA_CR_DIR_P2M |    /* Direction is peripheral to memory */ \
                        STM32_DMA_CR_TCIE         /* Enable Transmission Complete IRQ */
#endif // ADC

#endif // DMA

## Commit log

2016-03-21 + HW first
2016-03-23 + Sensor HW
2016-03-25 + Head started
2016-03-25 No IR TX
2016-04-01 + Sensor sent to manufacture * Head: barrel socket is here + armlet case
2016-04-01 Head sch seems completed
2016-04-05 Proceeding with ArmletG sch
2016-04-05 + gitignore
2016-04-05 Proceeding with armlet sch
2016-04-06 Single transistors
2016-04-10 + First blinking firmware for armlet L476
2016-04-11 + 3d works
2016-04-11 * Proceeding with armlets case
2016-04-11 Proceeding
2016-04-13 + GunRadio
2016-04-13 - everything exept radio and processor + 7-pin connector
2016-04-13 scematic nearly complited
2016-04-15 Armlet PCB in progress
2016-04-15 3 parts of armlet case
2016-04-16 Layout completed
2016-04-16 Tracing done
2016-04-17 + Armlet PCB sent to factory. * NSS 20101 footprints corrected to SC89-3 * Switched back to TopoR 6.1
2016-04-18 GunRadioPCB started
2016-04-18 + GunRadio nears completion
2016-04-28 Proceeding with sch
2016-05-01 + UART RX + I2C3 works with EE
2016-05-02 + i2c L476 work started. Bus scan done.
2016-05-03 + i2c seems working, though code is very dirty + Halt messaging
2016-05-03 Clean-up
2016-05-03 + i2c WriteWrite, Write
2016-05-03 + ee class
2016-05-03 * i2c 1 & 2 support added + MEMS work started
2016-05-03 GunRadio finished
2016-07-12 Last full-featured
2016-07-22 + I2C1 ok + gyro replies
2016-07-22 + mems work ok
2016-07-23 Test device for Kamill done
2016-08-21 + Blink On/Off
2016-08-21 + State machines
2016-08-27 Sch V2 done
2016-09-03 PCB2 done
2016-09-03 Kamill's code works
2016-09-03 sqrt -> sqrtf, sin -> sinf etc.
2016-09-03 Code from Kamill
2016-09-03 + Xotar's state machine
2016-09-03 + Xotar SM works * 12s instead of 3s
2016-09-14 * New PCB works
2016-09-19 + Calibration indication + Vibro Morse
2016-09-23 * Matching circuit done + Pill
2016-09-24 + First start
2016-09-25 + EEPROM + Get/Set ID
2016-09-26 + Main functional seems done
2016-09-27 + ADC works, but not completed
2016-09-27 + Oversampler works ok
2016-09-27 + Battery measurement Proceeding with indication
2016-09-28 Seems completed
2016-09-30 TheWord transmitted RC
2016-10-03 implement changes for Todmay with 4 strokes
2016-10-03 print deviation
2016-10-06 Proceeding with adc
2016-10-06 +Battery volume + charging indication + Get/Set ID
2016-10-09 Blink N times
2016-10-10 * Just another settings making him happy
2016-10-17 PillReset resets armlet + Pill read/write with UART
2016-10-19 + Pills
2016-10-19 - Some debug
2016-10-19 * New Xotar code + Battery discharged indication
2016-10-19 + Battery charging indication tested RC
2016-10-20 Release
2016-10-20 * Acc & Gyro reset several times Unstable
2016-10-26 In the Field
2016-11-26 + Tech report
2016-11-26 fix multiplication
2016-11-26 SoftReset
2016-11-28 new logic
2016-11-28 switch I and IV sign
2016-11-28 soft reset
2016-11-28 Some fix
2017-04-29 * Testing
2017-04-29 * 500kBit/s, FEC en
2017-06-03 + Calibration of Gyro and Acc * Radio under define
2017-06-03 + Adding calibration
2017-06-03 + Switch to Kamill's code
2017-06-03 Works at 72MHz
2017-09-13 PLL works using MSI to produce 72MHz
2019-02-24 Smth
